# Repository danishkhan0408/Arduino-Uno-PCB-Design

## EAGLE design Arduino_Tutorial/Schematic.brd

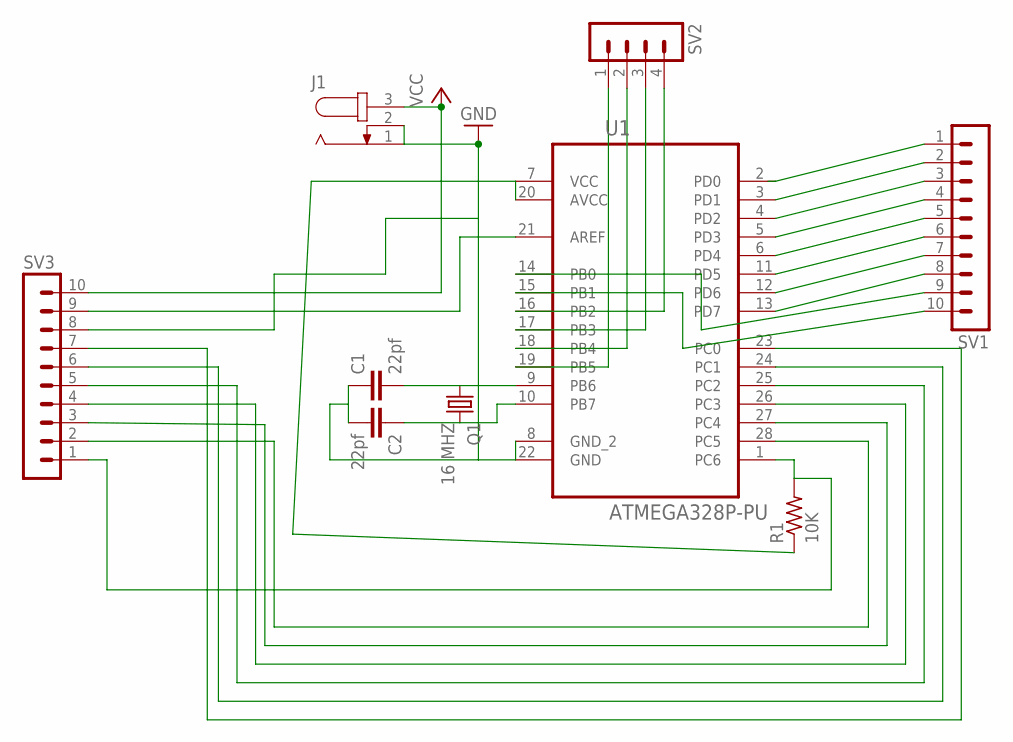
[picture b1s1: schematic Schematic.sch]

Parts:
C1, C2: 22pf; C025-024X044
J1: JACK-PLUG0; SPC4077
Q1: 16 MHZ; HC49/S
R1: 10K; 0207/10
SV1, SV3: MA10-1
SV2: MA04-1
U1: ATMEGA328P-PU; DIP254P762X457-28

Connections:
GND: C1.1, C2.2, J1.1, J1.2, SV3.8, U1.8 (GND_2), U1.22 (GND)
unnamed: C1.2, Q1.1, U1.9 (PB6)
unnamed: C2.1, Q1.2, U1.10 (PB7)
unnamed: SV1.1, U1.2 (PD0)
unnamed: SV1.2, U1.3 (PD1)
unnamed: R1.2, SV3.1, U1.1 (PC6)
unnamed: SV1.3, U1.4 (PD2)
unnamed: SV1.4, U1.5 (PD3)
unnamed: SV1.5, U1.6 (PD4)
unnamed: SV1.6, U1.11 (PD5)
unnamed: SV1.7, U1.12 (PD6)
unnamed: SV1.8, U1.13 (PD7)
unnamed: SV1.9, U1.14 (PB0)
unnamed: SV1.10, U1.15 (PB1)
unnamed: SV2.4, U1.16 (PB2)
unnamed: SV2.3, U1.17 (PB3)
unnamed: SV2.2, U1.18 (PB4)
unnamed: SV3.2, U1.28 (PC5)
unnamed: SV3.3, U1.27 (PC4)
unnamed: SV3.4, U1.26 (PC3)
unnamed: SV3.5, U1.25 (PC2)
unnamed: SV3.6, U1.24 (PC1)
unnamed: SV3.7, U1.23 (PC0)
unnamed: SV3.9, U1.21 (AREF)
unnamed: SV2.1, U1.19 (PB5)
VCC: J1.3, R1.1, SV3.10, U1.7 (VCC), U1.20 (AVCC)

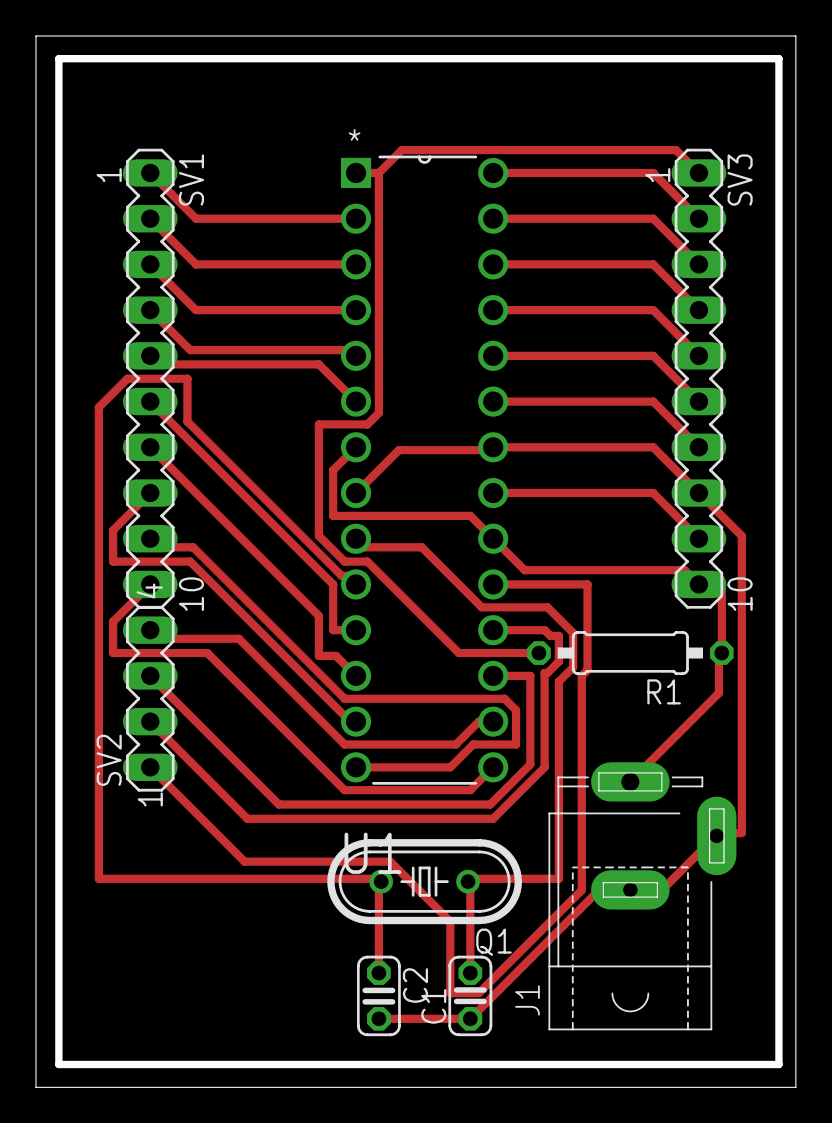
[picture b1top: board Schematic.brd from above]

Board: 2 copper layers, 41.8 x 58.0 mm, 9 parts (0 on the bottom side), 26 nets.

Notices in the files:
Arduino_Tutorial/Schematic.brd:
© 2017
